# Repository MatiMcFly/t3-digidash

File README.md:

# 🛻 T3 DigiDash -- Digital dashboard for the VW T3

(C) 2026 Matthias Schär, Rinaldo Leone, Timon Burkard

This is a project work part of the CAS Embedded Systems at FHNW Brugg-Windisch.

## Docs

Documentation, specification etc. can be found in [docs](docs/) directory.

## FW

This project consists of three firmware projects:

- [Disco](fw/disco/) -- ST Discovery Kit: STM32H747I-DISCO
- [Nucleo](fw/nucleo/) -- ST Nucleo Board: NUCLEO-H755ZI-Q
- [ESP](fw/esp/) -- Seeed ESP Board: ESP-C3

## HW

This project consists of four hardware projects:

- [disco-tft-adapter](hw/disco-tft-adapter/) -- Discovery Board TFT Adapter
- [t3-harness-adapter](hw/t3-harness-adapter/) -- T3 Wiring harness adapter
- [measurement-circuits](hw/measurement-circuits/) -- Collects all of the measurement circuits used
- [signal-emulator](hw/signal-emulator/) -- Sensor signal emulator (used for testing and demonstration)

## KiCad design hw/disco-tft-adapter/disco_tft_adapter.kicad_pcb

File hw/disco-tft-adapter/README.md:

# 🖥️ Discovery Board TFT Adapter

This project contains the KiCad hardware design for a TFT display adapter designed to connect a TFT panel (GX040R-30MB-A1ICNL9707) to an STMicroelectronics STM32H747I Discovery Kit.

The adapter board includes circuitry to interface the display with the Discovery board, including a TPS61169 LED driver for the display backlight.

## 🔌 Connectivity between DISCO board and GX040R display

- according to the manufacturer, the display has to be connected as follows: Board (DP/N0) to LCD (DP/N1) and (DP/N1) to (DP/N3). A previous revision A of this board has gotten this wrong. D0 of the board has been connected to D0 of the TFT and D1 of the board to D1 of the TFT.
- CTP (capacitive touch display) functionalities (I2C, INT, ...) are not used

## 📚 Datasheets and Documentation

All relevant datasheets, manuals, and reference documents can be found in this [Google Drive folder](https://drive.google.com/drive/folders/1Etk3SSePW-oP0WRn9YrgEl5WCk2nYt2u?usp=sharing).

### 📋 Document Overview:

* **`disco_tft_adapter.pdf`** - The schematic for this adapter board project.
* **`GX040R-30MB-A1(V1).pdf`** - Datasheet for the TFT display panel used with this adapter.
* **`ICNL_9707_Datasheet...pdf`** - Datasheet for the ICNL9707, the display driver IC integrated into the TFT panel (might be obsolete)
* **`tps61169.pdf`** - Datasheet for the Texas Instruments TPS61169, the WLED driver IC used on this adapter for the display backlight.
* **`stm32h747-datasheet.pdf`** - Electrical characteristics and pinout for the STM32H747 microcontroller.
* **`stm32h747-ref-manual.pdf`** - Detailed reference manual for the STM32H747 MCU peripherals and registers.
* **`stm32h747-prog-manual.pdf`** - Programming manual detailing the architecture and instruction set for the STM32H747.
* **`mb1166-default-a09-schematic.pdf`** - Schematic for the MB1166 base board of the STM32H7 Discovery kit.
* **`mb1248-h747i-d03-schematic.pdf`** - Schematic for the MB1248 CPU board of the STM32H747I-DISCO kit.
* **`um2411-discovery-kit-...pdf`** - Official user manual (UM2411) for the STM32H747I-DISCO Discovery kit.
* **`JD9365DA-H3_User_Guide_Preliminary_V0.00_20200827.pdf` - User guide for the display driver. This is the last version that was received from the contact person at the display manufacturer.

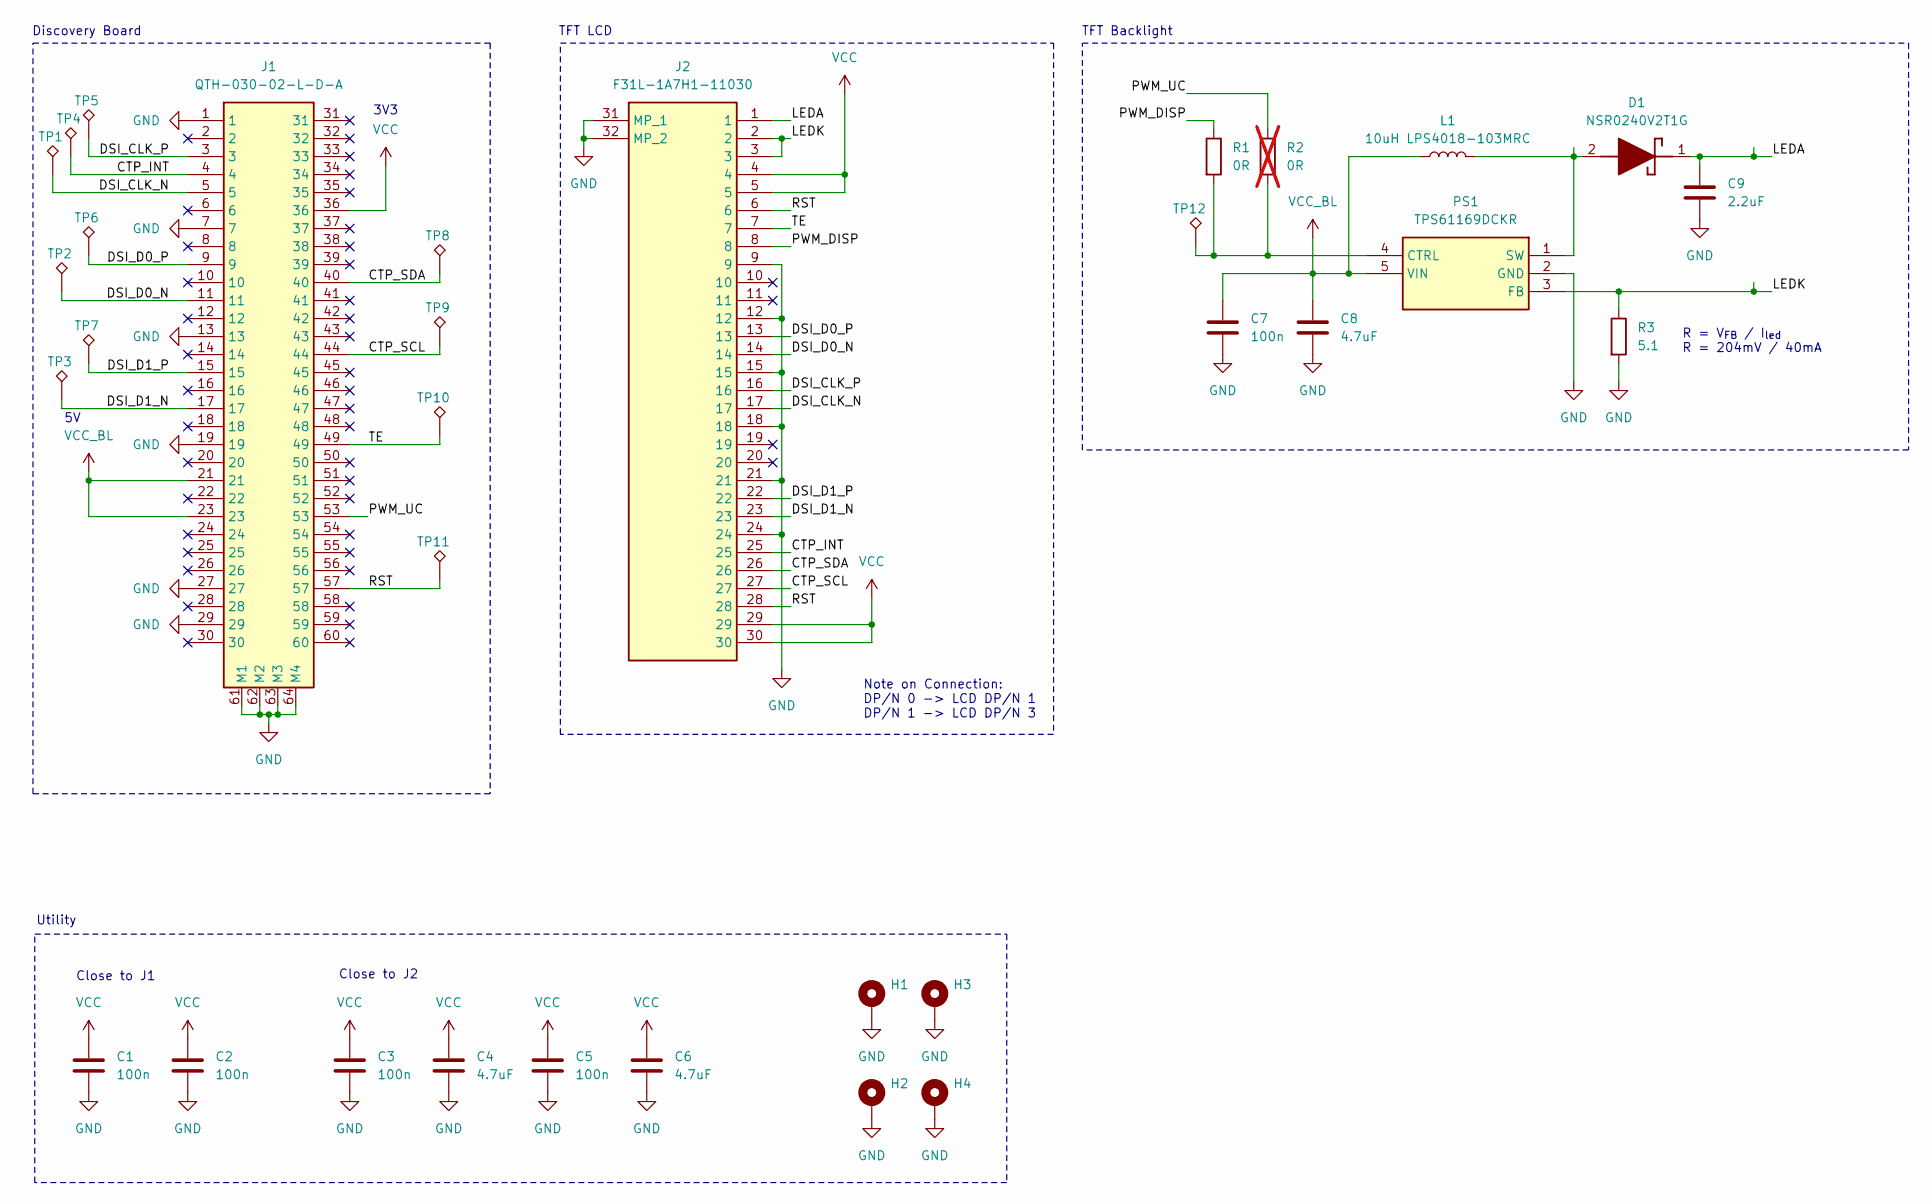
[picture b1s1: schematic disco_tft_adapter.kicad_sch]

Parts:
C1, C2, C3, C5, C7: 100n; C_0603_1608Metric; Mouser Part Number 603-C0603MRY5V9BB104
C4, C6, C8: 4.7uF; C_0805_2012Metric_Pad1.18x1.45mm_HandSolder; Mouser Part Number 581-08055D475KAT2A
C9: 2.2uF; C_0805_2012Metric_Pad1.18x1.45mm_HandSolder; Mouser Part Number 603-CC805KKX5R9BB225
D1: NSR0240V2T1G; SODFL1608X70N; Mouser Part Number 863-NSR0240V2T1G
H1, H2, H3, H4: MountingHole_Pad; MountingHole_4.5mm_Pad_TopBottom
J1: QTH-030-02-L-D-A; QTH-030-XX-Y-D-A; Mouser Part Number 200-QTH03002LDA
J2: F31L-1A7H1-11030; F31L1A7H111030; Mouser Part Number 649-F31L-1A7H1-11030
L1: 10uH LPS4018-103MRC; L_Coilcraft_1515SQ-47N; Mouser Part Number 994-LPS4018-103MRC
PS1: TPS61169DCKR; SOT65P210X110-5N; Mouser Part Number 595-TPS61169DCKR
R1: 0R; R_0603_1608Metric; Mouser Part Number 71-RCA06030000ZSEASR
R2: 0R; R_0603_1608Metric; Mouser Part Number 71-RCA06030000ZSEASR; not fitted
R3: 5.1; R_1206_3216Metric; Mouser Part Number 71-CRCW12065R10FKEA
TP1, TP2, TP3, TP4, TP5, TP6, TP7, TP8, TP9, TP10, TP11, TP12: TestPoint_Alt; TestPoint_TP_D0.5mm

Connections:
/CTP_INT: J1.4, J2.25, TP4.1 (1_1)
/CTP_SCL: J1.44, J2.27, TP9.1 (1_1)
/CTP_SDA: J1.40, J2.26, TP8.1 (1_1)
/DSI_CLK_N: J1.5, J2.17, TP1.1 (1_1)
/DSI_CLK_P: J1.3, J2.16, TP5.1 (1_1)
/DSI_D0_N: J1.11, J2.14, TP2.1 (1_1)
/DSI_D0_P: J1.9, J2.13, TP6.1 (1_1)
/DSI_D1_N: J1.17, J2.23, TP3.1 (1_1)
/DSI_D1_P: J1.15, J2.22, TP7.1 (1_1)
/LEDA: C9.1, D1.1 (K), J2.1
/LEDK: J2.2, J2.3, PS1.3 (FB), R3.1
/PWM_DISP: J2.8, R1.1
/PWM_UC: J1.53, R2.1
/RST: J1.57, J2.6, J2.28, TP11.1 (1_1)
/TE: J1.49, J2.7, TP10.1 (1_1)
GND: C1.2, C2.2, C3.2, C4.2, C5.2, C6.2, C7.2, C8.2, C9.2, H1.1 (1_1), H2.1 (1_1), H3.1 (1_1), H4.1 (1_1), J1.1, J1.7, J1.13, J1.19, J1.27, J1.29, J1.61 (M1), J1.62 (M2), J1.63 (M3), J1.64 (M4), J2.9, J2.12, J2.15, J2.18, J2.21, J2.24, J2.31 (MP_1), J2.32 (MP_2), PS1.2 (GND), R3.2
unnamed: D1.2 (A), L1.2, PS1.1 (SW)
unnamed: PS1.4 (CTRL), R1.2, R2.2, TP12.1 (1_1)
VCC: C1.1, C2.1, C3.1, C4.1, C5.1, C6.1, J1.36, J2.4, J2.5, J2.29, J2.30
VCC_BL: C7.1, C8.1, J1.21, J1.23, L1.1, PS1.5 (VIN)

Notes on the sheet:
3V3
Close to J1
Discovery Board
Close to J2
TFT Backlight
R = V_{FB} / I_{led} R = 204mV / 40mA
TFT LCD
Note on Connection: DP/N 0 -> LCD DP/N 1 DP/N 1 -> LCD DP/N 3
Utility

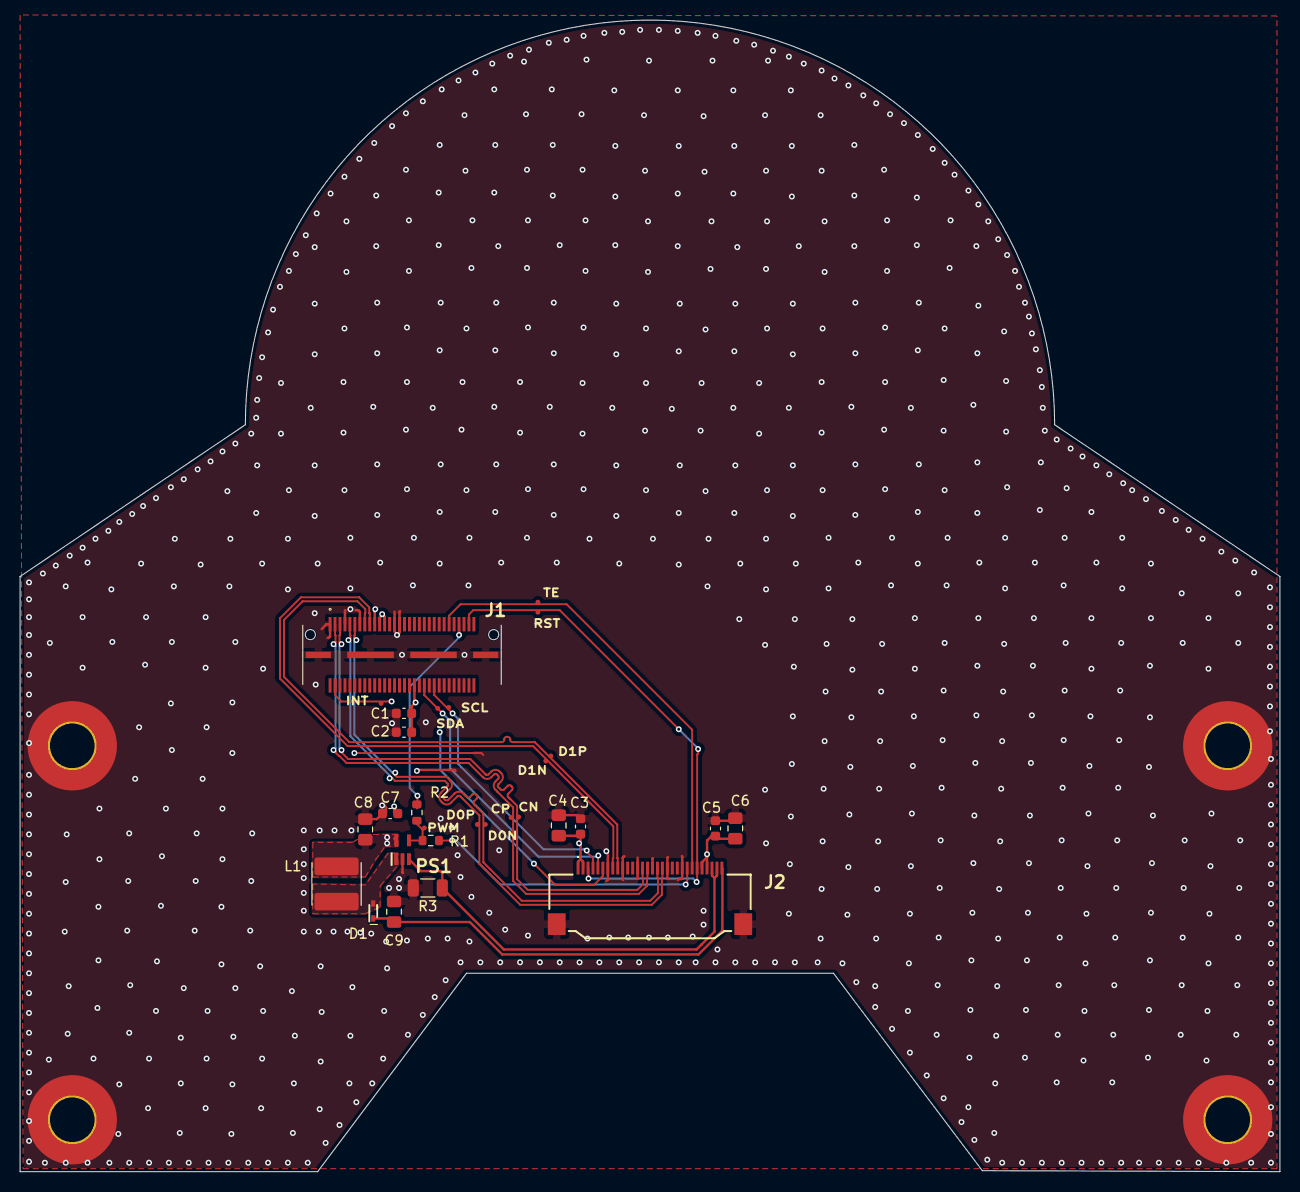
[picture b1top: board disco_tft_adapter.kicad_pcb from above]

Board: 4 copper layers, 127.0 x 116.1 mm, 33 parts (0 on the bottom side), 20 nets.

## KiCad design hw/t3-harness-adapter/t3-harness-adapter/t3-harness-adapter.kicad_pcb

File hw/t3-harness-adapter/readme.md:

## T3 Wiring harness adapter
This KiCAD project contains an adapter which can be used to retrieve the electrical signals from a VW T3 wiring harness.

The PCB has a board edge connector which adapts to the T3 dash wiring harness plug. All signals available are routed to pin headers for usage with other electronics, such as a STM32 development kit.

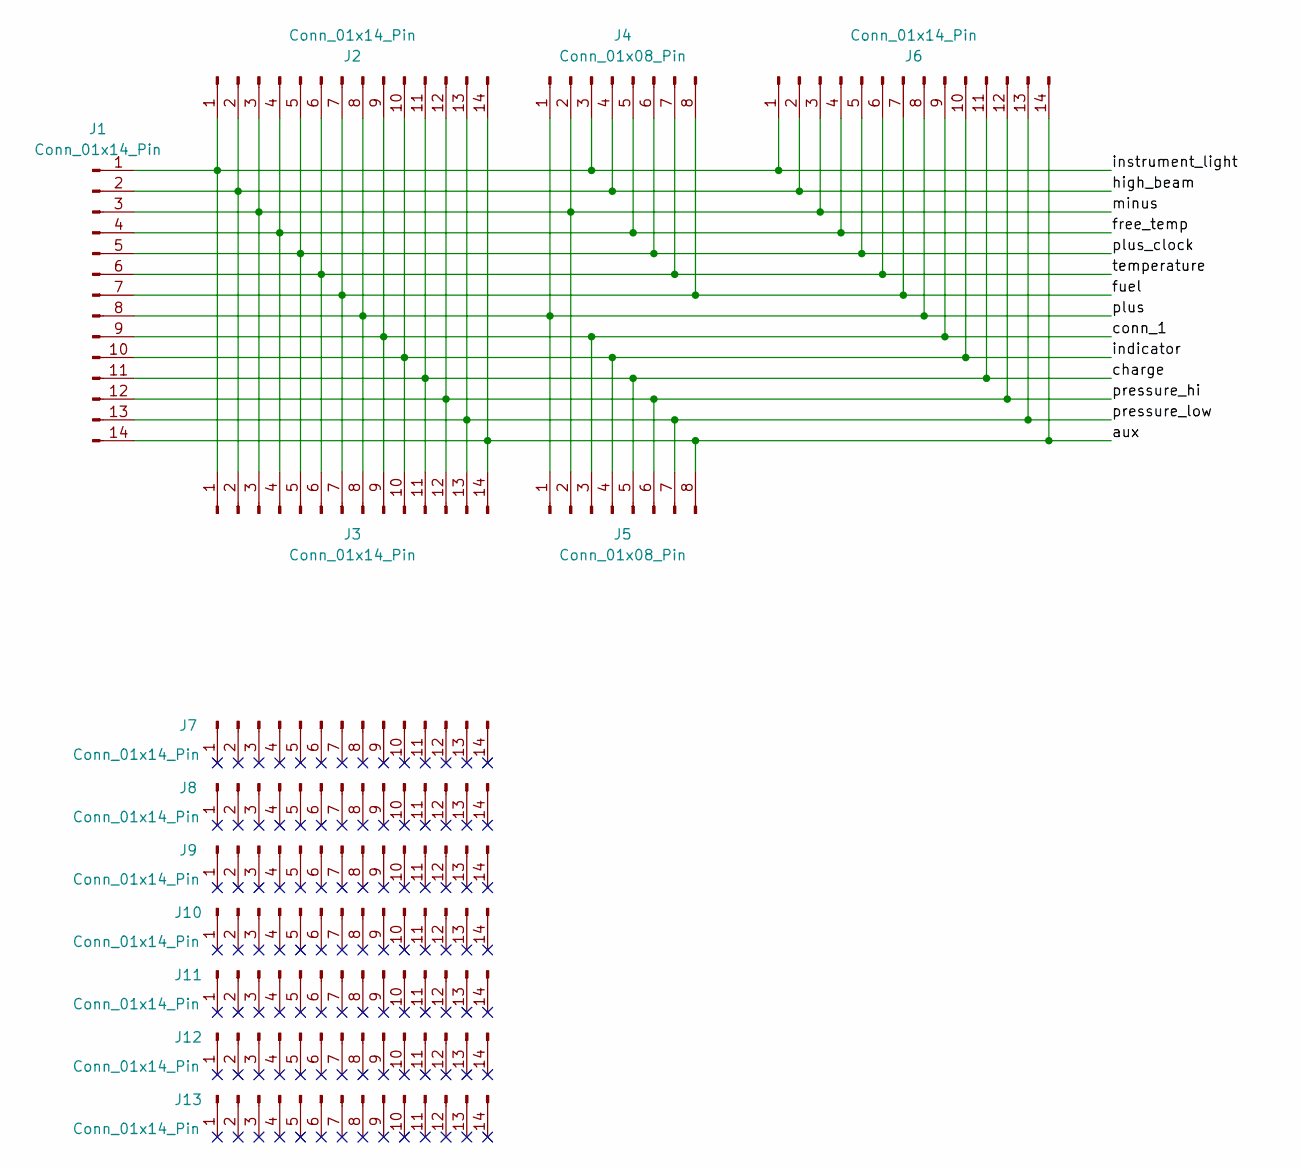
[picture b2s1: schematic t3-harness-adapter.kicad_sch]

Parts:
J1: Conn_01x14_Pin; t3-harness-edge
J2, J3, J6, J7, J8, J9, J10, J11, J12, J13: Conn_01x14_Pin; PinHeader_1x14_P2.54mm_Vertical
J4, J5: Conn_01x08_Pin; PinHeader_2x04_P2.54mm_Vertical

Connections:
/aux: J1.14, J2.14, J3.14, J5.8, J6.14
/charge: J1.11, J2.11, J3.11, J5.5, J6.11
/conn_1: J1.9, J2.9, J3.9, J5.3, J6.9
/free_temp: J1.4, J2.4, J3.4, J4.5, J6.4
/fuel: J1.7, J2.7, J3.7, J4.8, J6.7
/high_beam: J1.2, J2.2, J3.2, J4.4, J6.2
/indicator: J1.10, J2.10, J3.10, J5.4, J6.10
/instrument_light: J1.1, J2.1, J3.1, J4.3, J6.1
/minus: J1.3, J2.3, J3.3, J4.2, J5.2, J6.3
/plus: J1.8, J2.8, J3.8, J4.1, J5.1, J6.8
/plus_clock: J1.5, J2.5, J3.5, J4.6, J6.5
/pressure_hi: J1.12, J2.12, J3.12, J5.6, J6.12
/pressure_low: J1.13, J2.13, J3.13, J5.7, J6.13
/temperature: J1.6, J2.6, J3.6, J4.7, J6.6

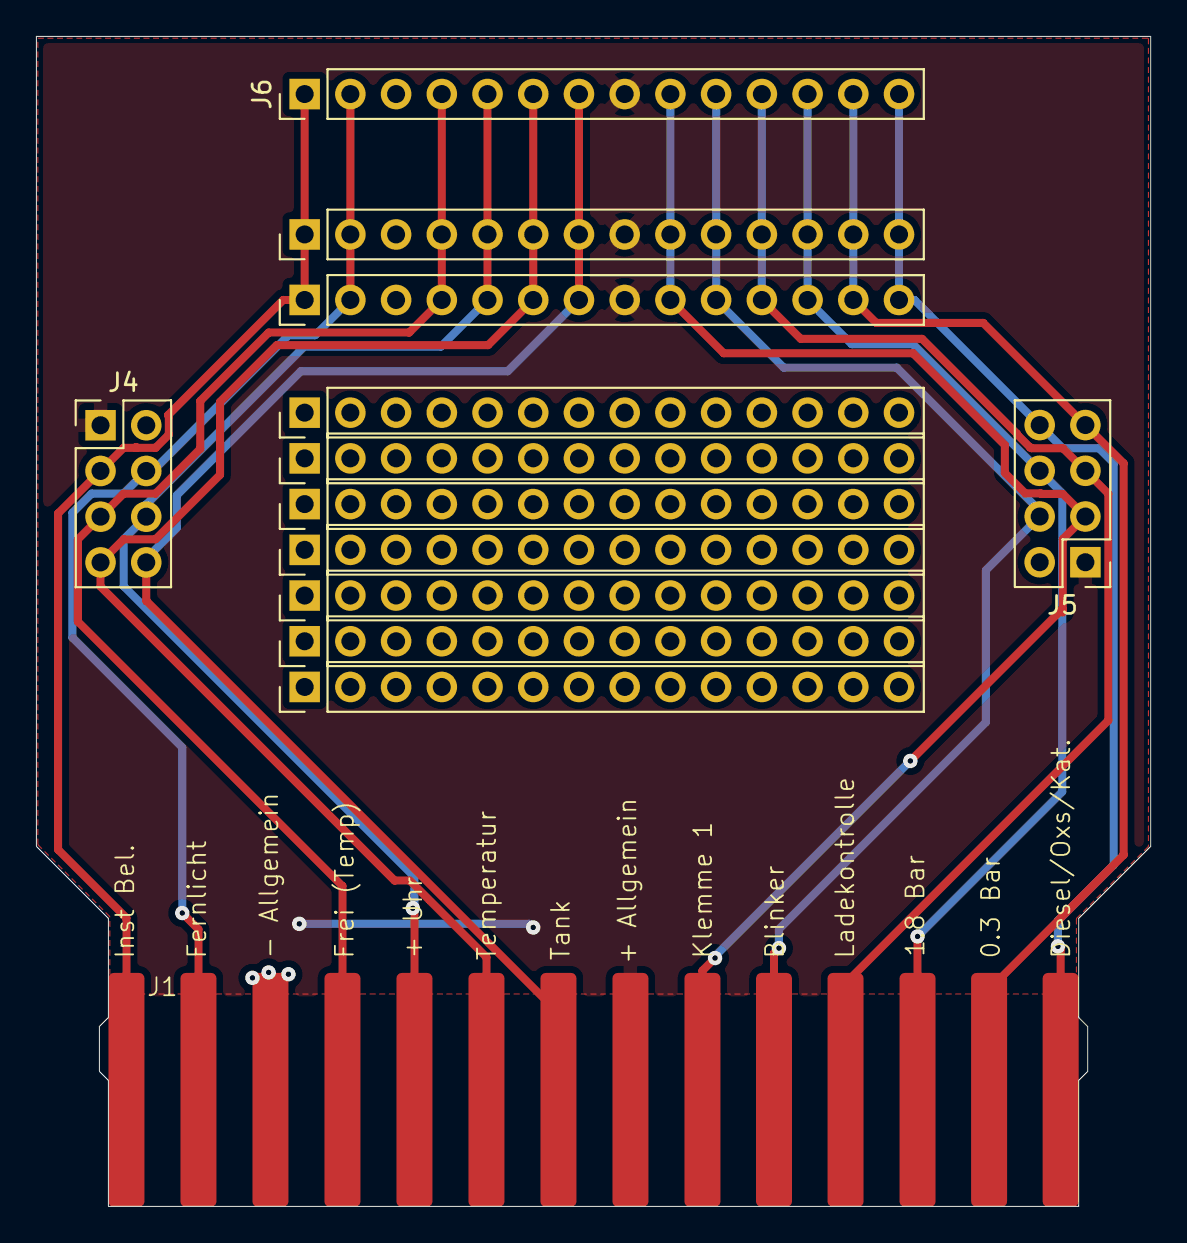
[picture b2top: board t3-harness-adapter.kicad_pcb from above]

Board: 2 copper layers, 61.9 x 65.0 mm, 13 parts (0 on the bottom side), 14 nets.

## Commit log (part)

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2026-03-30 initial commit containing a VSCode compatible CMake project
2026-03-30 [app] added main application entry point, toggles backlight on and off every second
2026-03-31 [hw] added DSI host for display to CM7 - enabled DSIHOST in video mode - enabled LTDC - moved ownership of SDRAM to CM7 - setup framebuffer on CM7
2026-04-22 [proj] move app.c and app.h to application folder
2026-04-22 [disp] extract display code and add it to its own module
2026-05-13 [wip] finally the display shows something.. however not the thing initially expected
2026-05-13 [wip] checkerboard visible, woop woop! Still have to cleanup .ioc
2026-05-17 [ci/esp] added build pipeline
    Just to make sure, at PR, that the ESP project is buildable.
2026-05-18 [proj] initial commit
2026-05-18 [proj] initial setup, added board edge connector for harness adapter
2026-05-18 [pcb] component placement
2026-05-18 [pcb] added layout
2026-05-22 [general/structure] moved repo `Disco_TFT_Adapter` into `hw/` directory
2026-05-22 [general/structure] added `docs/` directory
    Can be used for documentation, specification etc. Preferably in MD format.
2026-05-22 [docs] updated README
2026-05-22 [hw/t3-harness-adapter/output] setup output folder structure
2026-05-22 [hw/t3-harness-adapter/schematic] slight adjustment of positioning
2026-05-22 [hw/measurement-circuits] added formulas to calculate physical values
2026-05-22 [doc] update readme
2026-05-22 [doc] added sensor calculations to a markdown file
2026-05-22 [fw/esp] sent tank level as string
2026-05-22 [fw/esp] splitted uart parser from esp code
2026-05-22 [fw/esp] changes to parser. Implemented first structure to recieve data like defined
2026-05-22 [fw/esp] implemented first BLE example for water temperature and battery voltage. Used Standard UUID for battery
2026-05-22 [fw/esp] splitted code in different modules
2026-05-23 [doc/specification] more details for discovery kit
2026-05-23 [doc/specification] added picture of esp32 diagramm
2026-05-23 [fw/esp-testapp] done changes to try to communicate to app
2026-05-23 [doc/specification] modified ESP Diagramm block. Optional part is now gray marked
2026-05-23 [doc/specification] fixed typo
2026-05-23 [doc/specification] added ESP32 diagram
2026-05-23 [fw/esp-testapp] actual code is able to send data to RoboRemo app. App shows on level indicator the watertemperatur. ID of the level indicator is WT
2026-05-23 [fw/nucleo/mx] use UART3 only by M4, add UART1 for M7
    Also, M4 is marked as initializer in CubeMX, so it does not need to
    manually initialize the UART3 anymore.
2026-05-23 [fw/nucleo] introduced `shared.h`
    Shared header file between M4 and M7.
2026-05-23 [fw/nucleo] implemented IPC
    IPC (inter process communication) from M4 to M7
    FreeRTOS message buffer in shared SRAM4 is used:
    - 0x38000000: `__ipc_mb_struct_start__`
    - 0x38000080: `__ipc_mb_storage_start__`
    For this the cache is disabled.
    HSEM1 is used to send notification from M4 to M7 when a new message
2026-05-23 [fw/nucleo] delay to ensure start-up sequence
    M4 needs to initialize the message buffer before M7 can run.
    For now, lets do with a simple 1 s delay. In the future, maybe a
    more sophisticated approach can be implemented
2026-05-23 [fw/nucleo/m7] use agreed UART formatting
    ```
    <id>:<value>;
    ```
    This is how Disco and ESP are expecting the UART frames to arrive.
2026-05-23 [hw/emulator] added
    Simple sensor signal emulator.
    Will be used for testing and for demonstration, as part of the project
    presentation.
2026-05-23 [doc/minor] follow same convention for all README files
    Convention is with upper case: `README.md`
2026-05-23 [doc] added README for `hw/measurement-circuits`
2026-05-25 [fw/esp-remotexy] first trial with remotexy app
2026-05-25 [fw/esp-remotexy] uncommented logs
2026-05-29 [wip] updated ioc so that the main code is generated properly again
2026-05-29 [wip] display refresh rate increased to 60 Hz
2026-05-29 [fw/nucleo/m4] added implementation for sensor 04 (fuel level)
2026-05-29 [fw/nucleo/m4] fix: use unsigned for ADC value
2026-05-29 [fw/nucleo/m4/minor] explicitly mark unused parameters
2026-05-29 [fw/nucleo/mx] added sensor 04 (fuel level) on ADC1 CH5
2026-05-29 [fw/nucleo/m4] conversion: implemented conversion for sensor 01 (coolant temperature)
2026-05-29 [fw/nucleo/m4] refactoring: dedicated function to handle ring buffer
    Also we need to be able to have more than 255 elements in the ring
    buffer, because for the fuel level we want to have a moving average
    over approx. 30..60 s = 300..600 samples.
2026-05-29 [fw/nucleo/m4/minor] removed unused import
2026-05-29 [fw/disco/project] removed launch and cmake files from the .gitignore so the project doesn't have to be set up on every device
2026-05-29 [fw/nucleo/m4/minor] get rid of magic numbers
2026-05-29 [fw/nucleo/m4/minor] more precise return type
    Functionally the same, but still, lets use the correct one acc. to
    FreeRTOS API documentation.
2026-05-29 [docs] Keep README of Nucleo/FW a bit simpler
2026-05-29 [hw/measurement-circuits] fix: formula for coolant temperature
2026-05-29 [fw/nucleo/m4] debug: added units to debug uart output
2026-05-29 chore: add FreeRTOS-Kernel V11.3.0 as submodule
2026-05-29 [fw/nucleo/m4] added binary sensors 05..08
    - Sensor 05: Turn signal
    - Sensor 06: High beam
    - Sensor 07: Oil pressure 0.3 bar
    - Sensor 08: Oil pressure 1.8 bar
    Binary sensor signal: High or low -- simply read via GPIO.
    In the filtering state a debounce is implemented. The M4 keeps reporting
2026-05-29 [fw/nucleo/m4] refactoring: separate ring buffer update and mean
    In the future we will will not always want to calculate the mean when
    we update the ring buffer, so lets separate it into two functions.
2026-05-29 [fw/nucleo/mx] added GPIO inputs for sensors 05..08
    - Sensor 05: Turn signal --> PD0
    - Sensor 06: High beam --> PD1
    - Sensor 07: Oil pressure 0.3 bar --> PD2
    - Sensor 08: Oil pressure 1.8 bar --> PD3
2026-05-29 [fw/nucleo/m4/minor] moved define
    Let put both queue-specific configurations in the same place: `app.h`
2026-05-29 [fw/nucleo/m4] increased queue size
    We now have more sensors, so lets give a some more buffer size.
2026-05-29 [fw/nucleo/m4/minor] changed order of parameter checks
    If `size = 0`, then `*index >= size` is always true. So makes a bit more
    sense to change the order of the parameter checks.
2026-05-29 [docs] updated README of FW/Nucleo
2026-05-29 [fw/disco/touchgfx] wip: initial bring-up of touchGFX and FreeRTOS
2026-05-29 [fw/disco/touchgfx] generated simulator and application code, builds and flashes
2026-05-30 [fw/disco/rtos] FreeRTOS bring up, calls touchGFX render task periodically so a test touchGFX image is shown
2026-05-30 [fw/esp-remotexy] modified UI widgets
2026-05-30 [fw/disco/touchGFX] make sure that the changes made (RTOS mappings, routing of SV handlers, ..) persist CubeMX code regeneration
2026-05-30 [fw/esp-remotexy] done some changes to fix issues. Code is building and flashing. UI is visible but doesn't change
2026-05-31 [fw/esp-remotexy] added ino file
2026-05-31 [fw/esp-remotexy] done adaptation for faster UART transfer.
2026-06-04 [fw/disco/touchGFX] enable external flash via QSPI, adding first real assets to display
2026-06-04 [minor] renaming: lets call it "DigiDash" consistently
2026-06-04 [fw/nucleo/m4] implemented sensor 02: rotation speed
    TIM2 is used to capture the duration between two pulses (resp. two
    rising edges) on GPIO PA0.
    The value is then put into the `queue_data_raw` in unit [pulses per minute].
    The conversion task then converts this value into RPM:
    - 1 RPM generates 4 pulses per minute
2026-06-04 [fw/disco/display] adjusting alignment, color correction, more test rectangles for debugging
2026-06-04 [fw/disco/assets] cleanup rpm images, remove debug rectangles
2026-06-04 [fw/esp-remotexy] new ui. Implemented scaling for recieved values
2026-06-04 [fw/nucleo/m4] refactoring: added dedicated function to start pulsed sensors
    Currently only one pulsed sensor, but who knows...
2026-06-04 [fw/nucleo/m4] rotation speed: handle timeout
    If we don't receive an input capture for 0.1 s, we assume that the
    motor is not running anymore (too low speed) and we put the value to 0.
    We know that we didn't receive an input capture, if, after 0.1 s we try
    to restart the timer and get a HAL error, indicating that the timer is
    still running. If we would have received a capture in the meantime,
    the time would have been stopped in the ISR.
2026-06-04 [fw/disco/display] enable permanent backlight at 100%
2026-06-04 [fw/disco/gui] remove test pattern, add needle animation
2026-06-05 [fw/nucleo/m4] sensor rotation speed: fully reset timer if timeout
    Otherwise, some non-zero values will still be reported even if the
    pulse frequency is below the measurement frequency (10 Hz).
2026-06-05 [fw/disco/util] enable caches on SDRAM, increase AXI priority of AXISRAM, lower SDRAM clock, move prefill of external memory into source and not in startup code
2026-06-05 [fw/disco/gui] added accessors to set the fuel level and coolant temperature
2026-06-05 [fw/disco/util] set axi interconnect prio to max for SDRAM, avoid sending display buffer when it is written to
2026-06-05 [fw/disco/gui] add test code for the leds
2026-06-05 [fw/nucleo/m4] filtering: reduced number of averaging samples for rotation speed
    5 samples is too much for rotation speed. For high RPM values, this
    is 0.5 s, for low RPM values this could go up to 5 s.
    Therefore, it was changed to 2 averaging samples.
2026-06-05 [fw/nucleo/m4] sensor rotation speed: increased timeout duration to 1 s
    Otherwise, if we already assume a speed of 0 after 0.1 s, the min.
    measurable speed is 20 pulses per second (as we need two edges for a
    valid measurement), which is 1200 pulses per minute, which is 300 RPM.
    300 RPM is too high, we need to be able to go lower (e.g., 50 RPM).
    Therefore, the timeout duration was increased from 0.1 to 1 s.
    Now we can go down to 30 RPM.
2026-06-05 [ci] added PR pipeline for FW/Disco
2026-06-06 [fw/disco/project] delete .cache folder from clangd
2026-06-06 [ci] added PR pipeline for FW/Disco
    (cherry picked from commit 148c1c341e6c041a9b6ab8c6ed358908e8a2451a)
2026-06-06 [fw/disco/init] fixed AXIbus priority setting being overwritten by CubeMX generator
2026-06-06 [fw/disco/hw] setup USART2
2026-06-06 [fw/disco/rtos] moved task definitionsinto separate file
2026-06-06 [fw/disco/uart] added parser
2026-06-06 [doc] fixed typo in README
2026-06-06 [fw/disco/gui] connect LEDs correctly to the received sensor data
2026-06-06 [fw/nucleo/minor] renamed API function names
    Each API function now has module name as prefix
2026-06-06 [fw/nucleo/m4/minor] removed unused header file includes
2026-06-06 [fw/disco/gui] initialise LED states
2026-06-06 [fw/disco/gui] piecewise linear representation of the rpm needle, since the segment 0 ... 1000 rpm is a bit shorter
2026-06-06 [fw/nucleo/m4] refactoring: made filtering module pure
    Filtering module should be pure (no static variables) in order for it to
    be easily unit-testable.
2026-06-06 [fw/nucleo/minor] specify task sizes in bytes. no functional change.
2026-06-09 [esp-remotexy] updated readme of esp and added new UI information
2026-06-10 [tools] added a plotter and live monitor for the motor_rpm, the data is extracted from the nucleo debug output
2026-06-11 [fw/esp-remotexy] adjusted readme. Modified UI so that only one oil lamp is shown. Implemented and tested following functionality: Oil lamp is only red if one of the oil values (0.3bar or 1.8bar) is 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
2026-06-12 [fw/nucleo/conversion] fixed conversion rate from pulses per minute to rpm: one motor revolution = 2 pulses, not 4
2026-06-12 [fw/disco/gui] fix oil lamp. 1.8 bar not connected -> only use 0.3 bar
2026-06-12 [fw/disco/gui] added alternative middle display which shows numerical sensor values
2026-06-12 [fw/disco/gui] update new UI element with real values
2026-06-13 [fw/nucleo/testing] fixed failing unit test, had to adjust conversion factor
2026-06-13 [esp-remotexy] chanign oil lamp behaviour. 0.3 off => light on. 0.3 on => light off. Changed advertisement name in T3 Digidash
